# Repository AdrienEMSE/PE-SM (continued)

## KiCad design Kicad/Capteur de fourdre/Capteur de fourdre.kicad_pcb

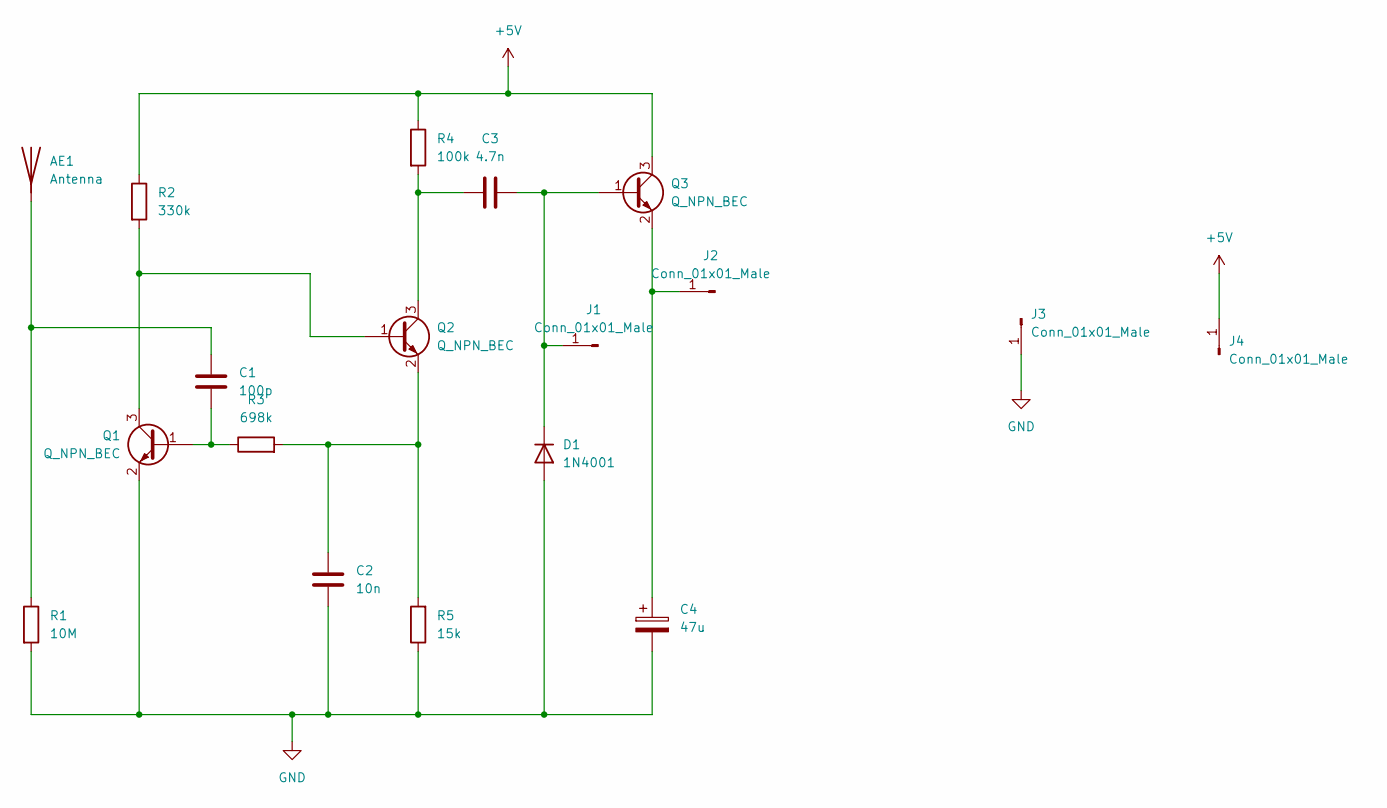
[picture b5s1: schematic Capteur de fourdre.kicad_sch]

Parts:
AE1: Antenna; PinHeader_1x01_P2.54mm_Vertical
C1: 100p; C_0603_1608Metric
C2: 10n; C_0805_2012Metric
C3: 4.7n; C_0603_1608Metric
C4: 47u; CP_Elec_6.3x5.8
D1: 1N4001; D_SOD-123
J1, J2, J3, J4: Conn_01x01_Male; PinHeader_1x01_P2.54mm_Vertical
Q1, Q2, Q3: Q_NPN_BEC; SOT-23
R1: 10M; R_0805_2012Metric
R2: 330k; R_0805_2012Metric
R3: 698k; R_0805_2012Metric
R4: 100k; R_0805_2012Metric
R5: 15k; R_0805_2012Metric

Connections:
+5V: J4.1, Q3.3 (C), R2.1, R4.1
GND: C2.2, C4.2, D1.2 (A), J3.1, Q1.2 (E), R1.2, R5.1
unnamed: AE1.1 (A), C1.1, R1.1
unnamed: C1.2, Q1.1 (B), R3.1
unnamed: C2.1, Q2.2 (E), R3.2, R5.2
unnamed: C3.1, Q2.3 (C), R4.2
unnamed: C3.2, D1.1 (K), J1.1, Q3.1 (B)
unnamed: C4.1, J2.1, Q3.2 (E)
unnamed: Q1.3 (C), Q2.1 (B), R2.2

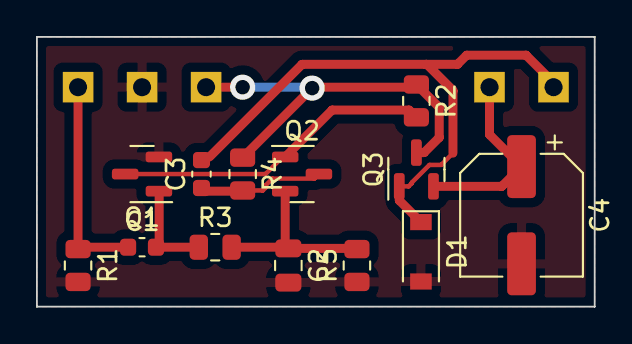
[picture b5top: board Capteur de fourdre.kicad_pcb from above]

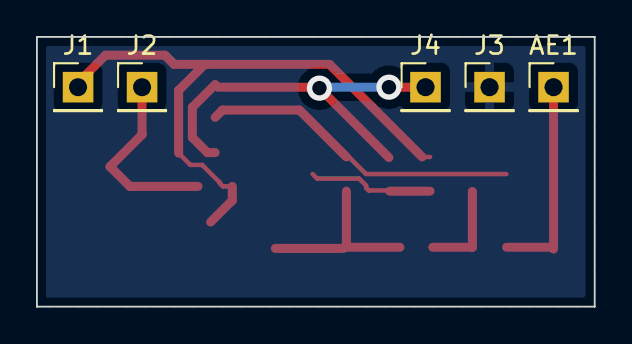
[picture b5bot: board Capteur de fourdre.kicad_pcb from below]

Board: 2 copper layers, 31.0 x 15.0 mm, 18 parts (5 on the bottom side), 9 nets.

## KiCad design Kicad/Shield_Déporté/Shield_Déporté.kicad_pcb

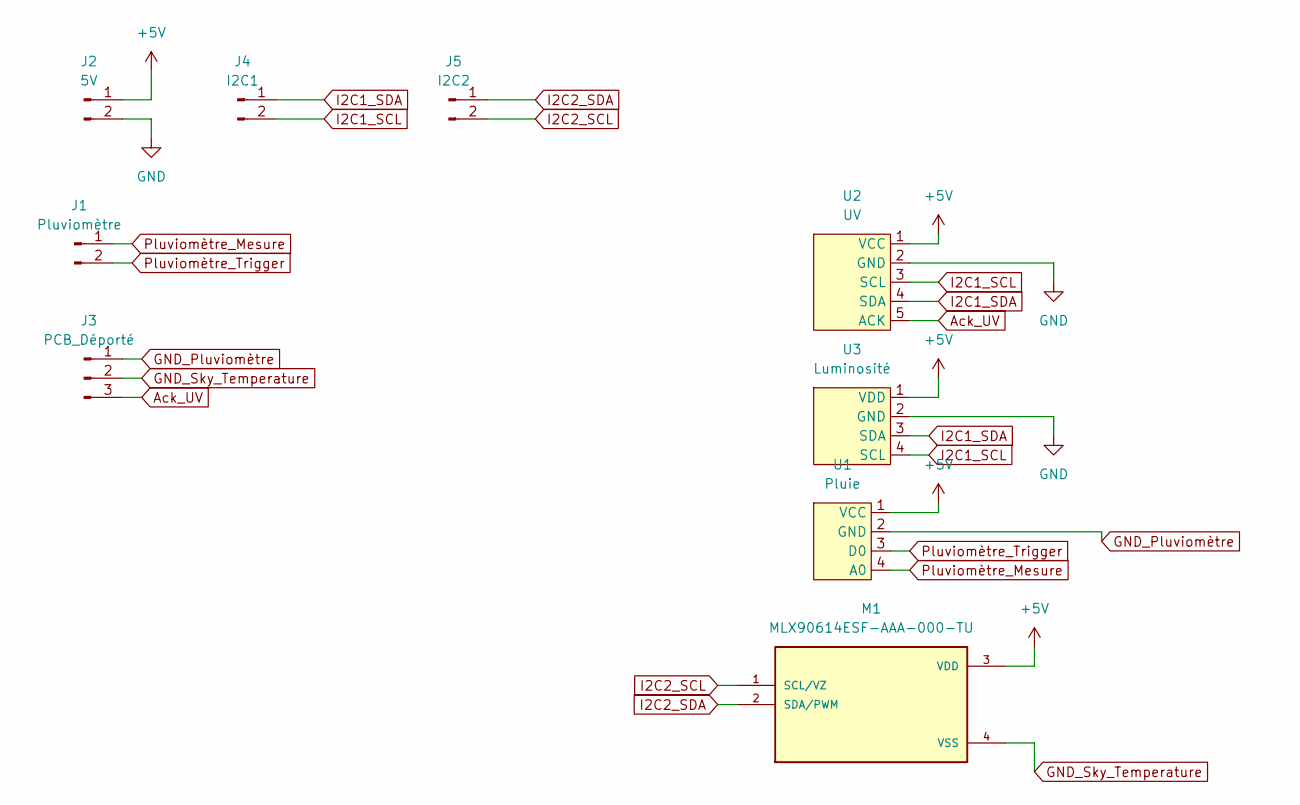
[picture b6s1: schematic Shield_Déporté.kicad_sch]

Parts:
J1: Pluviomètre; JST_EH_B2B-EH-A_1x02_P2.50mm_Vertical
J2: 5V; JST_EH_B2B-EH-A_1x02_P2.50mm_Vertical
J3: PCB_Déporté; JST_EH_B3B-EH-A_1x03_P2.50mm_Vertical
J4: I2C1; JST_EH_B2B-EH-A_1x02_P2.50mm_Vertical
J5: I2C2; JST_EH_B2B-EH-A_1x02_P2.50mm_Vertical
M1: MLX90614ESF-AAA-000-TU; TO254P942H425-4; PARTREV 13
U1: Pluie
U2: UV
U3: Luminosité; Luminosite

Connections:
+5V: J2.1, M1.3 (VDD), U1.1 (VCC), U2.1 (VCC), U3.1 (VDD)
Ack_UV: J3.3, U2.5 (ACK)
GND: J2.2, U2.2 (GND), U3.2 (GND)
GND_Pluviomètre: J3.1, U1.2 (GND)
GND_Sky_Temperature: J3.2, M1.4 (VSS)
I2C1_SCL: J4.2, U2.3 (SCL), U3.4 (SCL)
I2C1_SDA: J4.1, U2.4 (SDA), U3.3 (SDA)
I2C2_SCL: J5.2, M1.1 (SCL/VZ)
I2C2_SDA: J5.1, M1.2 (SDA/PWM)
Pluviomètre_Mesure: J1.1, U1.4 (A0)
Pluviomètre_Trigger: J1.2, U1.3 (D0)

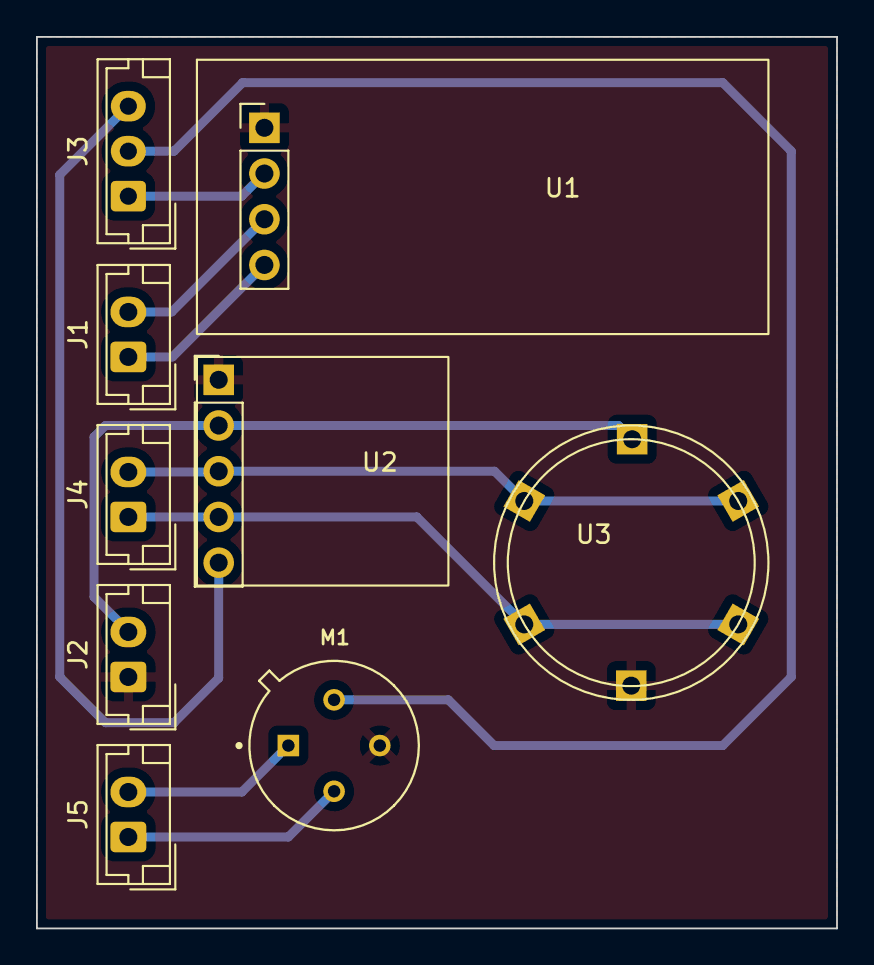
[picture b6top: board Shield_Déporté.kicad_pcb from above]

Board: 2 copper layers, 44.5 x 49.5 mm, 9 parts (0 on the bottom side), 11 nets.

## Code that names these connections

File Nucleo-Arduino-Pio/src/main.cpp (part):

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static const int anemo_phase_1 = A1, anemo_phase_2 = A2;
static const int capteur_de_foudre = A3;

static const int ack_uv = PE12;


//tous les pins suivants servent à couper l'alimentation aux composants lorsqu'ils ne sont pas utilisés
static const int pin_big_blue_button = USER_BTN;

static const int alimentation_gps = D8;
static const int alimentation_dht = D9;
static const int alimentation_skytemp = D10;
static const int alimentation_pluvio = PA7;
static const int alimentation_lumi = D12;
static const int alimentation_ESP = D13;
static const int alimentation_anemo = PE10;

/*----------PARAMS----------*/

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

HardwareSerial Serial6(D0, D1); // Liaison série vers ESP
TwoWire Wire2(PB11, PB10);  //le MLX90614 est sur sa propre ligne I2C car il entrait en conflit avec les autres capteurs
msg_ESP_class aenvoyer(&Serial6); //classe regroupant les données récupérées sur les capteurs


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  pinMode(pin_big_blue_button,INPUT_PULLDOWN);
  
  pinMode(alimentation_anemo,OUTPUT);
  pinMode(alimentation_dht,OUTPUT);
  pinMode(alimentation_skytemp,OUTPUT);
  pinMode(alimentation_lumi,OUTPUT);
  pinMode(alimentation_ESP,OUTPUT);
  pinMode(alimentation_gps,OUTPUT);
  pinMode(alimentation_pluvio, OUTPUT);

  pinMode(capteur_de_foudre,INPUT_FLOATING);

  pinMode(ack_uv, INPUT_FLOATING);

  pinMode(anemo_phase_1, INPUT);
  pinMode(anemo_phase_2, INPUT);
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
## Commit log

2023-03-01 added main folders with Readme
2023-03-01 added ESP32 folder
2023-03-01 init pio project
2023-03-01 GPS_lib_ok
2023-03-01 removed useless code
2023-03-01 capteur fonctionnel
2023-03-01 Air_quality_Ok
2023-03-02 rainOmeter Ok
2023-03-02 RH OK
2023-03-02 commOK
2023-03-02 missed line
2023-03-02 GPS MANUAL
2023-03-02 corrected typo
2023-03-02 It compiles
2023-03-03 Commenting
2023-03-03 I2CSCAN
2023-03-03 fonctionne
2023-03-03 Add code for esp82
2023-03-03 Clean
2023-03-03 test
2023-03-03 gpsnotOK
2023-03-03 Revert "test"
    This reverts commit 91f736de96b436d706b10980af67c7b41052b489.
2023-03-03 Revert "Revert "test""
    This reverts commit 388f2b878e428fdda2ae8d899d1dc690cff40094.
2023-03-03 GPS_OK_ONLYDATETIME
2023-03-03 Formatting
2023-03-03 Low power ccs
2023-03-06 added CRC verif
2023-03-06 Code for CO2 & PM2.5 sensors, com with raspberry
2023-03-06 Added crc for serial
2023-03-06 added struct
2023-03-06 Add file for UART communication with Nucleo
    Allows UART communication with Nucleo, which controls C02 and PM2.5 sensors
2023-03-06 aligned MSG_ESP
2023-03-06 added comment
2023-03-07 FIXED CRC
2023-03-07 Add class for msg_ESP
2023-03-07 Merging
2023-03-07 added send
2023-03-07 added safesend in main
2023-03-07 Comm OK
2023-03-08 added safeSend
2023-03-08 added alim
2023-03-08 removed useless define
2023-03-08 comment
2023-03-08 added alim anemo
2023-03-08 test lumi
2023-03-09 Add Com between ESP82 and STM & msg struct
2023-03-09 Add code to read MQTT server and save in CSV
2023-03-09 updated struct for crc
2023-03-09 Corrected msg_ESP.cpp
2023-03-10 correcting comm pb
2023-03-10 mode deepSleeep(STOP), arbre d'horloge réduit, power_voltage_scale de 1 à 3 et désactivation mode overdrive
2023-03-10 Separate gps and sensors messages
2023-03-10 Read and send data & gps messages
2023-03-10 ss.end()
2023-03-10 PLLP_DIV2 => PLLP_DIV4
2023-03-10 PLLN 216 => 192 [temps de démarrage de malade]
2023-03-10 Pas possible de descendre la fréquence plus bas
2023-03-10 commentaire
2023-03-10 Finalizing merge
2023-03-10 added depedancy
2023-03-10 corrected conflict
2023-03-15 Editing main to send messages to ThingsBoard
2023-03-16 PCBs des différentes parties de la station
2023-03-16 resolution probleme envoi + petites modifications
2023-03-16 Moved Wifi ESP in lib
2023-03-16 added gps bypass
2023-03-16 commentaires
2023-03-16 button
2023-03-16 Script to send indoor sensors data to Thingsboard
2023-03-16 ajout wakeup from thunder
2023-03-16 Interrupt thunder ok
2023-03-22 switched from nmos to pmos for gps
2023-03-22 Added power toggle for lumi sensor
2023-03-22 corrected
2023-03-22 oublié le pin ack_uv
2023-03-23 ajouté support anémomètre
2023-03-23 alimentation pin anemo + delay?
2023-03-23 ALIM PLUVIO SAPRISTI
2023-03-23 delay DHT avant utilisation TCS
2023-03-24 added 3D file
2023-03-27 status update pour redémarrage ESP + lat/long GPS
2023-03-27 ligne en trop avant fin setup
2023-03-28 Rename Thingsboard_TxRx_Nucleo.py to get_indoor_data
2023-03-28 Rename get_indoor_data to get_indoor_data.py
2023-03-28 delay avant MLX dans setup si #ifndef DEBUG
2023-03-29 3D files
2023-03-29 Add 3D pieces for server's case
2023-03-29 added ressources
2023-03-29 added datasheet
2023-03-29 added slides
